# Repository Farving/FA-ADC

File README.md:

# FA-ADC
Farving Acoustic ADC /w FA-Core interface

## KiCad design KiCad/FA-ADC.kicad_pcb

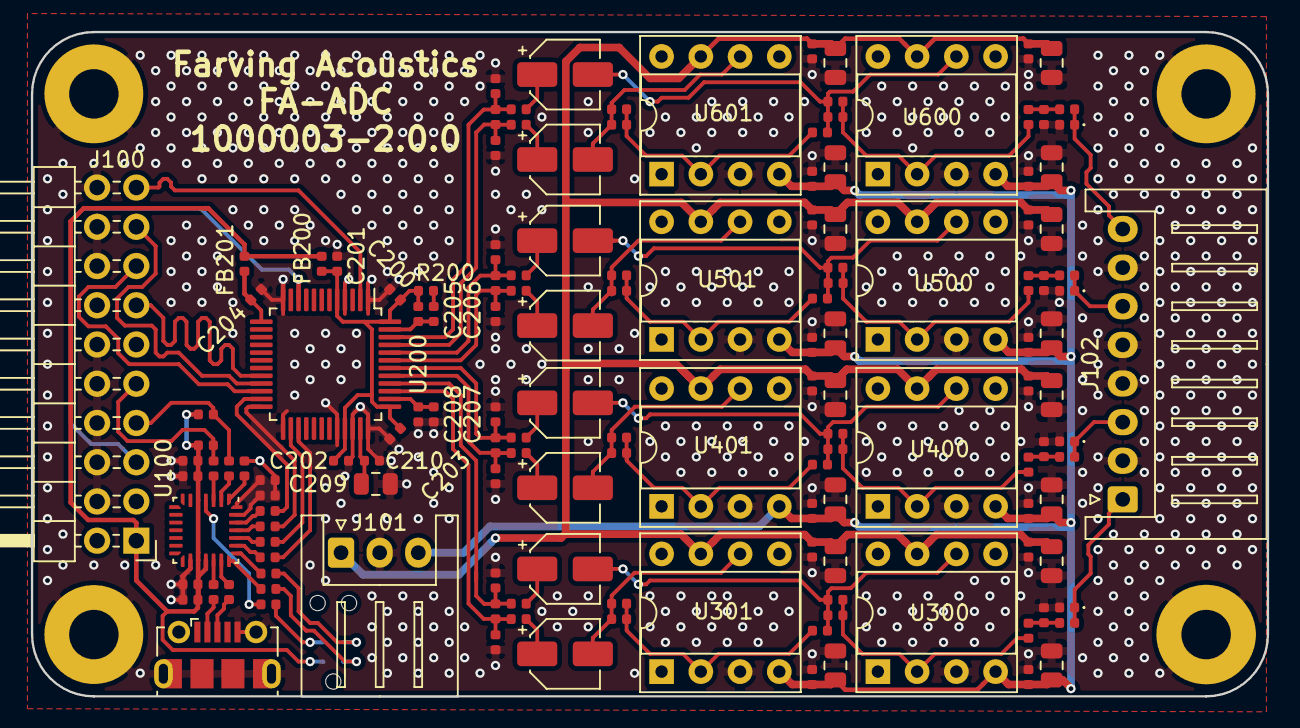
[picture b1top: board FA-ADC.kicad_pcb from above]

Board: 2 copper layers, 80.0 x 43.0 mm, 146 parts (1 on the bottom side), 80 nets.

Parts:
C1: 4.7u; C_0402_1005Metric
C2, C200, C201, C202, C203, C204, C208, C210, C307, C309, C311, C313, C315, C407, C409, C411, C413, C415, C507, C509, C511, C513, C515, C607, C609, C611, C613, C615: 100n; C_0402_1005Metric
C3: 10n; C_0402_1005Metric
C4: 1u; C_0402_1005Metric
C205: 390p; C_0402_1005Metric
C206: 5.6n; C_0402_1005Metric
C207: 10u; C_0402_1005Metric
C209: 47u; C_0805_2012Metric
C300, C400, C500, C600: 100p; C_0402_1005Metric
C301, C302, C401, C402, C501, C502, C601, C602: 120p; C_0402_1005Metric
C303, C304, C403, C404, C503, C504, C603, C604: 10u; CP_Elec_4x5.4
C305, C306, C405, C406, C505, C506, C605, C606: 1n; C_0402_1005Metric
C308, C310, C312, C314, C408, C410, C412, C414, C508, C510, C512, C514, C608, C610, C612, C614: 10u; C_0805_2012Metric
D300, D400, D500, D600: TBD; D_0402_1005Metric
FB200, FB201: 600Z; L_0402_1005Metric
FB300, FB400, FB500, FB600: 600R; L_0402_1005Metric
J1: TC2030; Tag-Connect_TC2030-IDC-NL_2x03_P1.27mm_Vertical
J100: Conn_02x10_Odd_Even; PinHeader_2x10_P2.54mm_Horizontal
J101: JST_XH_S3B; JST_XH_S3B-XH-A_1x03_P2.50mm_Horizontal
J102: JST_XH_S8B; JST_XH_S8B-XH-A_1x08_P2.50mm_Horizontal
J103: USB_OTG; USB_Micro-B_Molex-105017-0001
PCB100: 70x43; PCB_Board_70x43
R1, R2: 2.2k; R_0402_1005Metric
R3, R4, R5, R6, R7, R9, R11, R14, R15: 100R; R_0402_1005Metric
R8: 10k; R_0402_1005Metric
R10, R12, R13, R16: 0R; R_0402_1005Metric
R200: 562R; R_0402_1005Metric
R300, R301, R302, R303, R400, R401, R402, R403, R500, R501, R502, R503, R600, R601, R602, R603: 5.76k; R_0402_1005Metric
R304, R305, R404, R405, R504, R505, R604, R605: 237R; R_0402_1005Metric
U100: STM32F042G4Ux; QFN-28_4x4mm_P0.5mm
U200: AD1974; LQFP-48_7x7mm_P0.5mm
U300, U301, U400, U401, U500, U501, U600, U601: AD797; DIP-8_W7.62mm_Socket

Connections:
+3V3: C1.1, C2.1, C3.1, C4.1, FB200.1, FB201.1, J1.1, J100.1, R1.1, R2.1, U100.5, U100.17, U100.18
+15V: C308.2, C309.2, C312.2, C313.2, C408.2, C409.2, C412.2, C413.2, C508.2, C509.2, C512.2, C513.2, C608.2, C609.2, C612.2, C613.2, J101.1, U300.7, U301.7, U400.7, U401.7, U500.7, U501.7, U600.7, U601.7
-15V: C310.1, C311.1, C314.1, C315.1, C410.1, C411.1, C414.1, C415.1, C510.1, C511.1, C514.1, C515.1, C610.1, C611.1, C614.1, C615.1, J101.3, U300.4, U301.4, U400.4, U401.4, U500.4, U501.4, U600.4, U601.4
/ADC/In_L0N: C305.2, C307.2, R304.1, U200.40
/ADC/In_L0P: C306.1, C307.1, R305.1, U200.39
/ADC/In_L1N: C505.2, C507.2, R504.1, U200.44
/ADC/In_L1P: C506.1, C507.1, R505.1, U200.43
/ADC/In_R0N: C405.2, C407.2, R404.1, U200.42
/ADC/In_R0P: C406.1, C407.1, R405.1, U200.41
/ADC/In_R1N: C605.2, C607.2, R604.1, U200.46
/ADC/In_R1P: C606.1, C607.1, R605.1, U200.45
/BOOT0: R8.1, U100.1
/ENABLE: J100.5, U200.10
/I2C_ADDR0: R16.1, U100.28
/I2C_ADDR1: R10.1, U100.27
/I2C_SCL: J100.9, R2.2, R4.2
/I2C_SDA: J100.7, R1.2, R3.2
/I2S_BCLK: J100.17, U200.21
/I2S_LRCLK: J100.15, U200.22
/I2S_MCLK: J100.19, U200.2
/I2S_SD0: J100.13, U200.20
/Left Buffer 1/In: D300.1, FB300.2, J102.1
/Left Buffer 2/In: D500.1, FB500.2, J102.6
/NRST: J1.3, R11.2
/Right Buffer 1/In: D400.1, FB400.2, J102.3
/Right Buffer 2/In: D600.1, FB600.2, J102.8
/SPI_CS: R9.1, U200.27
/SPI_MISO: R6.2, U200.24
/SPI_MOSI: R7.2, U200.23
/SPI_SCK: R5.2, U200.26
/SWCLK: J1.4, R15.1
/SWDIO: J1.2, R14.1
/USB_DM: J103.2, R12.1
/USB_DP: J103.3, R13.1
GND: C1.2, C2.2, C3.2, C4.2, C200.2, C201.2, C202.2, C203.2, C204.2, C207.2, C208.2, C209.2, C210.2, C300.1, C305.1, C306.2, C308.1, C309.1, C310.2, C311.2, C312.1, C313.1, C314.2, C315.2, C400.1, C405.1, C406.2, C408.1, C409.1, C410.2, C411.2, C412.1, C413.1, C414.2, C415.2, C500.1, C505.1, C506.2, C508.1, C509.1, C510.2, C511.2, C512.1, C513.1, C514.2, C515.2, C600.1, C605.1, C606.2, C608.1, C609.1, C610.2, C611.2, C612.1, C613.1, C614.2, C615.2, D300.2, D400.2, D500.2, D600.2, J1.5, J100.4, J100.6, J100.8, J100.10, J100.12, J100.14, J100.16, J100.18, J100.20, J101.2, J102.2, J102.4, J102.5, J102.7, J103.5, J103.6, PCB100.1, PCB100.2, PCB100.3, PCB100.4, R8.2, R10.2, R16.2, U100.16, U200.1, U200.4, U200.12, U200.25, U200.32, U200.34, U200.36, U300.3, U301.3, U400.3, U401.3, U500.3, U501.3, U600.3, U601.3
unnamed: C200.1, C201.1, C202.1, C203.1, C205.1, FB200.2, R200.1, U200.5, U200.33, U200.37, U200.48
unnamed: C204.1, FB201.2, U200.13
unnamed: C205.2, C206.2, U200.47
unnamed: C206.1, R200.2
unnamed: C207.1, C208.1, U200.38
unnamed: C209.1, C210.1, U200.35
unnamed: C300.2, FB300.1, R300.2
unnamed: C301.1, C303.2, R301.1, R302.1, U300.6
unnamed: C301.2, R300.1, R301.2, U300.2
unnamed: C302.1, C304.2, R303.1, U301.6
unnamed: C302.2, R302.2, R303.2, U301.2
unnamed: C303.1, R304.2
unnamed: C304.1, R305.2
unnamed: C400.2, FB400.1, R400.2
unnamed: C401.1, C403.2, R401.1, R402.1, U400.6
unnamed: C401.2, R400.1, R401.2, U400.2
unnamed: C402.1, C404.2, R403.1, U401.6
unnamed: C402.2, R402.2, R403.2, U401.2
unnamed: C403.1, R404.2
unnamed: C404.1, R405.2
unnamed: C500.2, FB500.1, R500.2
unnamed: C501.1, C503.2, R501.1, R502.1, U500.6
unnamed: C501.2, R500.1, R501.2, U500.2
unnamed: C502.1, C504.2, R503.1, U501.6
unnamed: C502.2, R502.2, R503.2, U501.2
unnamed: C503.1, R504.2
unnamed: C504.1, R505.2
unnamed: C600.2, FB600.1, R600.2
unnamed: C601.1, C603.2, R601.1, R602.1, U600.6
unnamed: C601.2, R600.1, R601.2, U600.2
unnamed: C602.1, C604.2, R603.1, U601.6
unnamed: C602.2, R602.2, R603.2, U601.2
unnamed: C603.1, R604.2
unnamed: C604.1, R605.2
unnamed: R3.1, U100.2
unnamed: R4.1, U100.3
unnamed: R5.1, U100.24
unnamed: R6.1, U100.25
unnamed: R7.1, U100.26
unnamed: R9.2, U100.23
unnamed: R11.1, U100.4
unnamed: R12.2, U100.19
unnamed: R13.2, U100.20
unnamed: R14.2, U100.21
unnamed: R15.2, U100.22

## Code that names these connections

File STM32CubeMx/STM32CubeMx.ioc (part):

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Mcu.Name=STM32F042G(4-6)Ux
Mcu.Package=UFQFPN28
Mcu.UserName=STM32F042G4Ux
PA11.Mode=Device
PA11.Signal=USB_DM
PA12.Mode=Device
PA12.Signal=USB_DP
PA13.Mode=Serial_Wire
PA13.Signal=SYS_SWDIO
PA14.Mode=Serial_Wire
PA14.Signal=SYS_SWCLK
PA15.Mode=NSS_Signal_Hard_Output
PA15.Signal=SPI1_NSS
PB3.Mode=Full_Duplex_Master
PB3.Signal=SPI1_SCK
PB4.Mode=Full_Duplex_Master
PB4.Signal=SPI1_MISO
PB5.Mode=Full_Duplex_Master
PB5.Signal=SPI1_MOSI
PB6.GPIOParameters=GPIO_Label
PB6.GPIO_Label=I2C_ADDR1
PB6.Signal=GPIO_Input
PB7.GPIOParameters=GPIO_Label
PB7.GPIO_Label=I2C_ADDR0
PB7.Signal=GPIO_Input
PB8.GPIOParameters=GPIO_Label
PB8.GPIO_Label=BOOT0
PB8.Signal=GPIO_Input
PF0-OSC_IN.Mode=I2C
PF0-OSC_IN.Signal=I2C1_SDA
PF1-OSC_OUT.Mode=I2C
PF1-OSC_OUT.Signal=I2C1_SCL
RCC.SYSCLKFreq_VALUE=48000000
RCC.SYSCLKSource=RCC_SYSCLKSOURCE_HSI48
board=custom

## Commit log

2020-03-25 Add AD1974 Schematic
    Add Input buffer
2020-06-30 Progress Commit
2020-11-10 Update for release
2020-11-10 Add STM32Cube file for fw
